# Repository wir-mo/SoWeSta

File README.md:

# SoWeSta
**So**lar powered **We**ather **Sta**tion

## PCB
You can view the pcb in your browser using [this link](https://kicanvas.org/?github=https%3A%2F%2Fgithub.com%2Fwir-mo%2FSoWeSta%2Ftree%2Fmain%2Fpcb)

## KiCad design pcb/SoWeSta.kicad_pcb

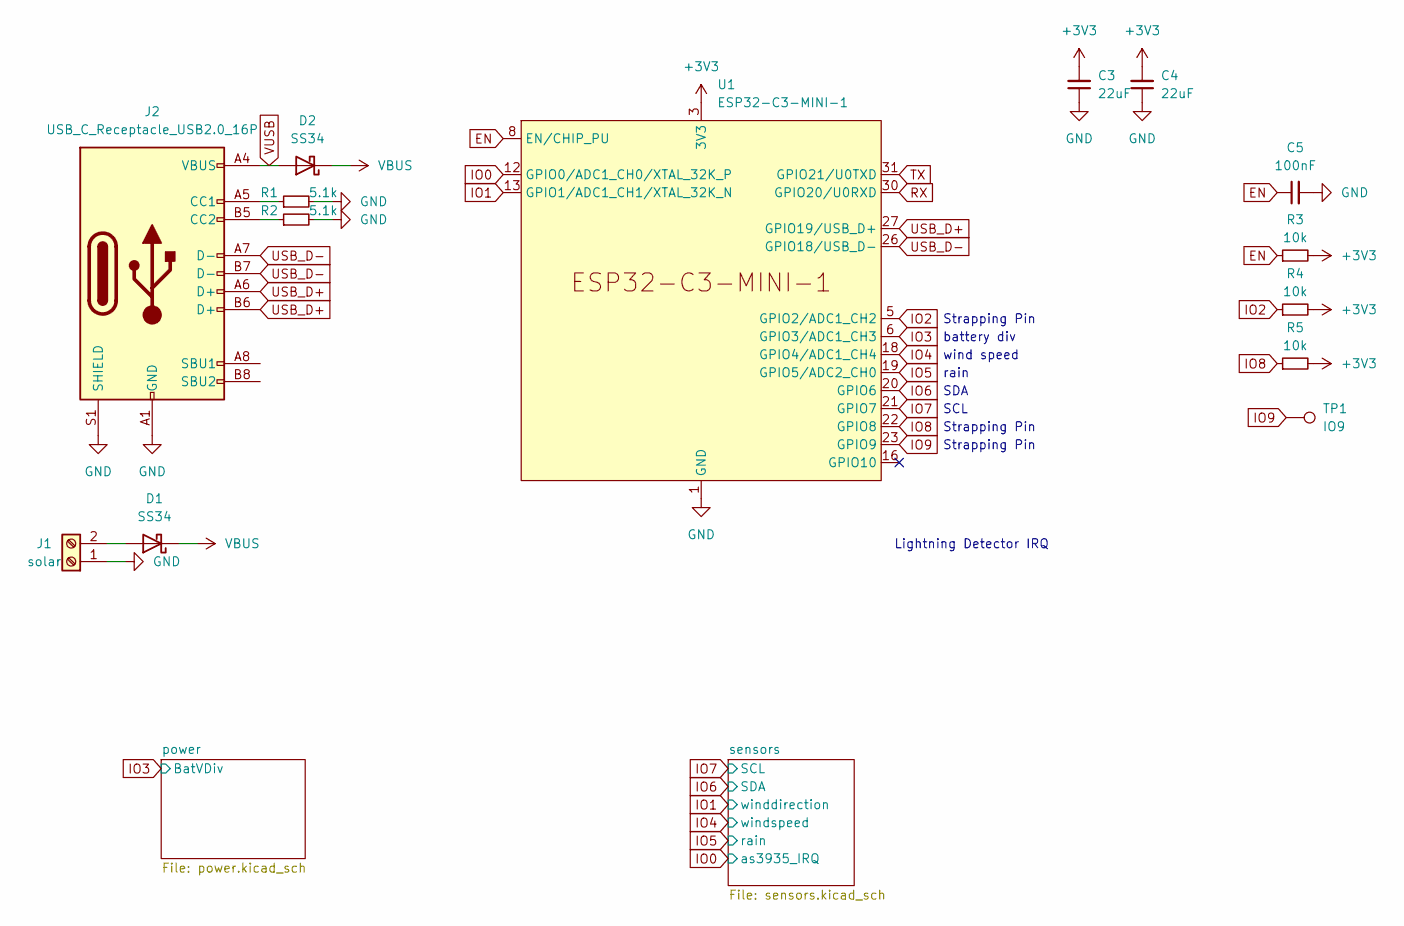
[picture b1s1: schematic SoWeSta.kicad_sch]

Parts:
C3, C4: 22uF; C_0603_1608Metric
C5: 100nF; C_0603_1608Metric
D1, D2: SS34; D_SMA
J1: solar; PhoenixContact_MC_1,5_2-G-3.5_1x02_P3.50mm_Horizontal
J2: USB_C_Receptacle_USB2.0_16P; USB_C_Receptacle_GCT_USB4105-xx-A_16P_TopMnt_Horizontal
R1, R2: 5.1k; R_0603_1608Metric
R3, R4, R5: 10k; R_0603_1608Metric
TP1: IO9; TestPoint_Pad_D1.0mm
U1: ESP32-C3-MINI-1

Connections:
+3V3: C3.2, C4.2, R3.2, R4.2, R5.2, U1.3 (3V3); also elsewhere on the board
EN: C5.1, R3.1, U1.8 (EN/CHIP_PU)
GND: C3.1, C4.1, C5.2, J1.1, J2.A1 (GND), J2.A12 (GND), J2.B1 (GND), J2.B12 (GND), J2.S1 (SHIELD), R1.2, R2.2, U1.1 (GND), U1.2 (GND), U1.11 (GND), U1.14 (GND), U1.36 (GND), U1.37 (GND), U1.38 (GND), U1.39 (GND), U1.40 (GND), U1.41 (GND), U1.42 (GND), U1.43 (GND), U1.44 (GND), U1.45 (GND), U1.46 (GND), U1.47 (GND), U1.48 (GND), U1.49 (GND), U1.50 (GND), U1.51 (GND), U1.52 (GND), U1.53 (GND); also elsewhere on the board
IO0: U1.12 (GPIO0/ADC1_CH0/XTAL_32K_P); also elsewhere on the board
IO1: U1.13 (GPIO1/ADC1_CH1/XTAL_32K_N); also elsewhere on the board
IO2: R4.1, U1.5 (GPIO2/ADC1_CH2)
IO3: U1.6 (GPIO3/ADC1_CH3); also elsewhere on the board
IO4: U1.18 (GPIO4/ADC1_CH4); also elsewhere on the board
IO5: U1.19 (GPIO5/ADC2_CH0); also elsewhere on the board
IO6: U1.20 (GPIO6); also elsewhere on the board
IO7: U1.21 (GPIO7); also elsewhere on the board
IO8: R5.1, U1.22 (GPIO8)
IO9: TP1.1, U1.23 (GPIO9)
unnamed: D1.2 (A), J1.2
unnamed: J2.A5 (CC1), R1.1
unnamed: J2.B5 (CC2), R2.1
RX: U1.30 (GPIO20/U0RXD); also elsewhere on the board
TX: U1.31 (GPIO21/U0TXD); also elsewhere on the board
USB_D+: J2.A6 (D+), J2.B6 (D+), U1.27 (GPIO19/USB_D+)
USB_D-: J2.A7 (D-), J2.B7 (D-), U1.26 (GPIO18/USB_D-)
VBUS: D1.1 (K), D2.1 (K); also elsewhere on the board
VUSB: D2.2 (A), J2.A4 (VBUS), J2.A9 (VBUS), J2.B4 (VBUS), J2.B9 (VBUS); also elsewhere on the board

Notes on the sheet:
SCL
battery div
wind speed
Lightning Detector IRQ
Strapping Pin
rain
SDA

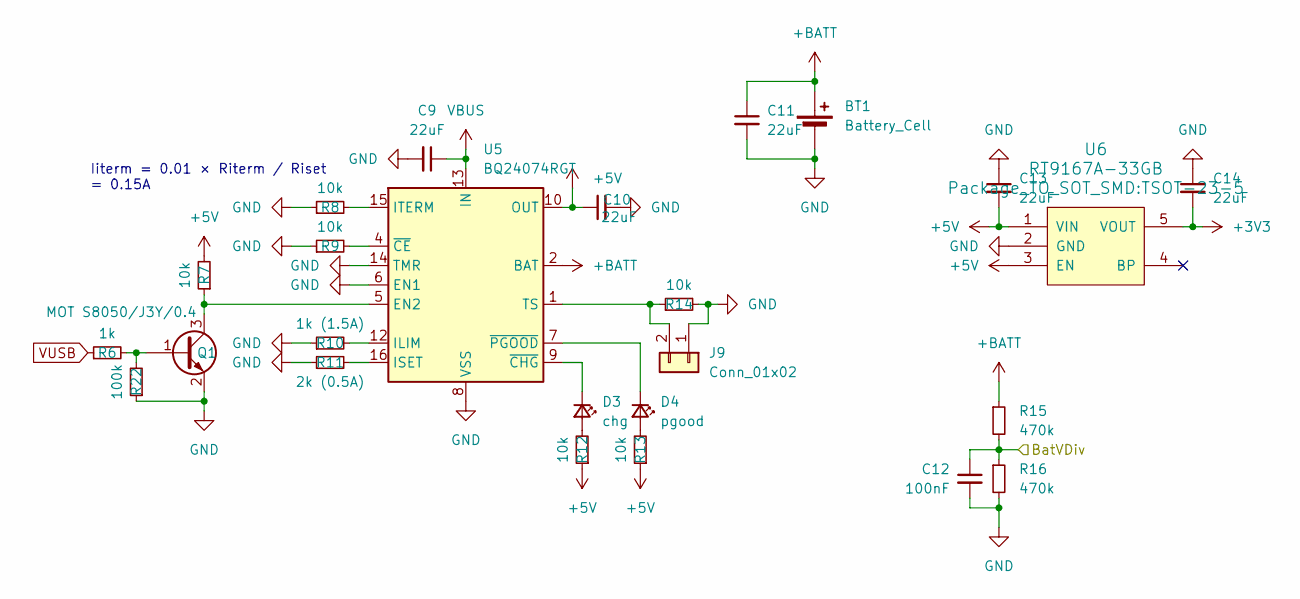
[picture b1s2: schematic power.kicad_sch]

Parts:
BT1: Battery_Cell; BH-18650-B1BA002
C9, C10, C11, C13, C14: 22uF; C_0603_1608Metric
C12: 100nF; C_0603_1608Metric
D3: chg; LED_0603_1608Metric
D4: pgood; LED_0603_1608Metric
J9: Conn_01x02; PinHeader_1x02_P2.54mm_Vertical
Q1: MOT S8050/J3Y/0.4; SOT-23
R6: 1k; R_0603_1608Metric
R7, R8, R9, R12, R13, R14: 10k; R_0603_1608Metric
R10: 1k (1.5A); R_0603_1608Metric
R11: 2k (0.5A); R_0603_1608Metric
R15, R16: 470k; R_0603_1608Metric
R22: 100k; R_0603_1608Metric
U5: BQ24074RGT; VQFN-16-1EP_3x3mm_P0.5mm_EP1.6x1.6mm
U6: RT9167A-33GB; TSOT-23-5

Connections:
+3V3: C14.2, U6.5 (VOUT); also elsewhere on the board
+5V: C10.1, C13.2, R7.2, R12.1, R13.1, U5.10 (OUT), U5.11 (OUT), U6.1 (VIN), U6.3 (EN); also elsewhere on the board
+BATT: BT1.1 (+), C11.1, R15.1, U5.2 (BAT), U5.3 (BAT)
GND: BT1.2 (-), C9.2, C10.2, C11.2, C12.2, C13.1, C14.1, J9.1, Q1.2 (E), R8.1, R9.1, R10.1, R11.1, R14.2, R16.2, R22.1, U5.6 (EN1), U5.8 (VSS), U5.14 (TMR), U5.17 (VSS), U6.2 (GND); also elsewhere on the board
IO3: C12.1, R15.2, R16.1; also elsewhere on the board
unnamed: D3.2 (A), R12.2
unnamed: D3.1 (K), U5.9 (~CHG)
unnamed: D4.2 (A), R13.2
unnamed: D4.1 (K), U5.7 (~PGOOD)
unnamed: J9.2, R14.1, U5.1 (TS)
unnamed: Q1.1 (B), R6.2, R22.2
unnamed: Q1.3 (C), R7.1, U5.5 (EN2)
unnamed: R10.2, U5.12 (ILIM)
unnamed: R11.2, U5.16 (ISET)
unnamed: R8.2, U5.15 (ITERM)
unnamed: R9.2, U5.4 (~CE)
VBUS: C9.1, U5.13 (IN); also elsewhere on the board
VUSB: R6.1; also elsewhere on the board

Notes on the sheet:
Iiterm = 0.01 × Riterm / Riset = 0.15A

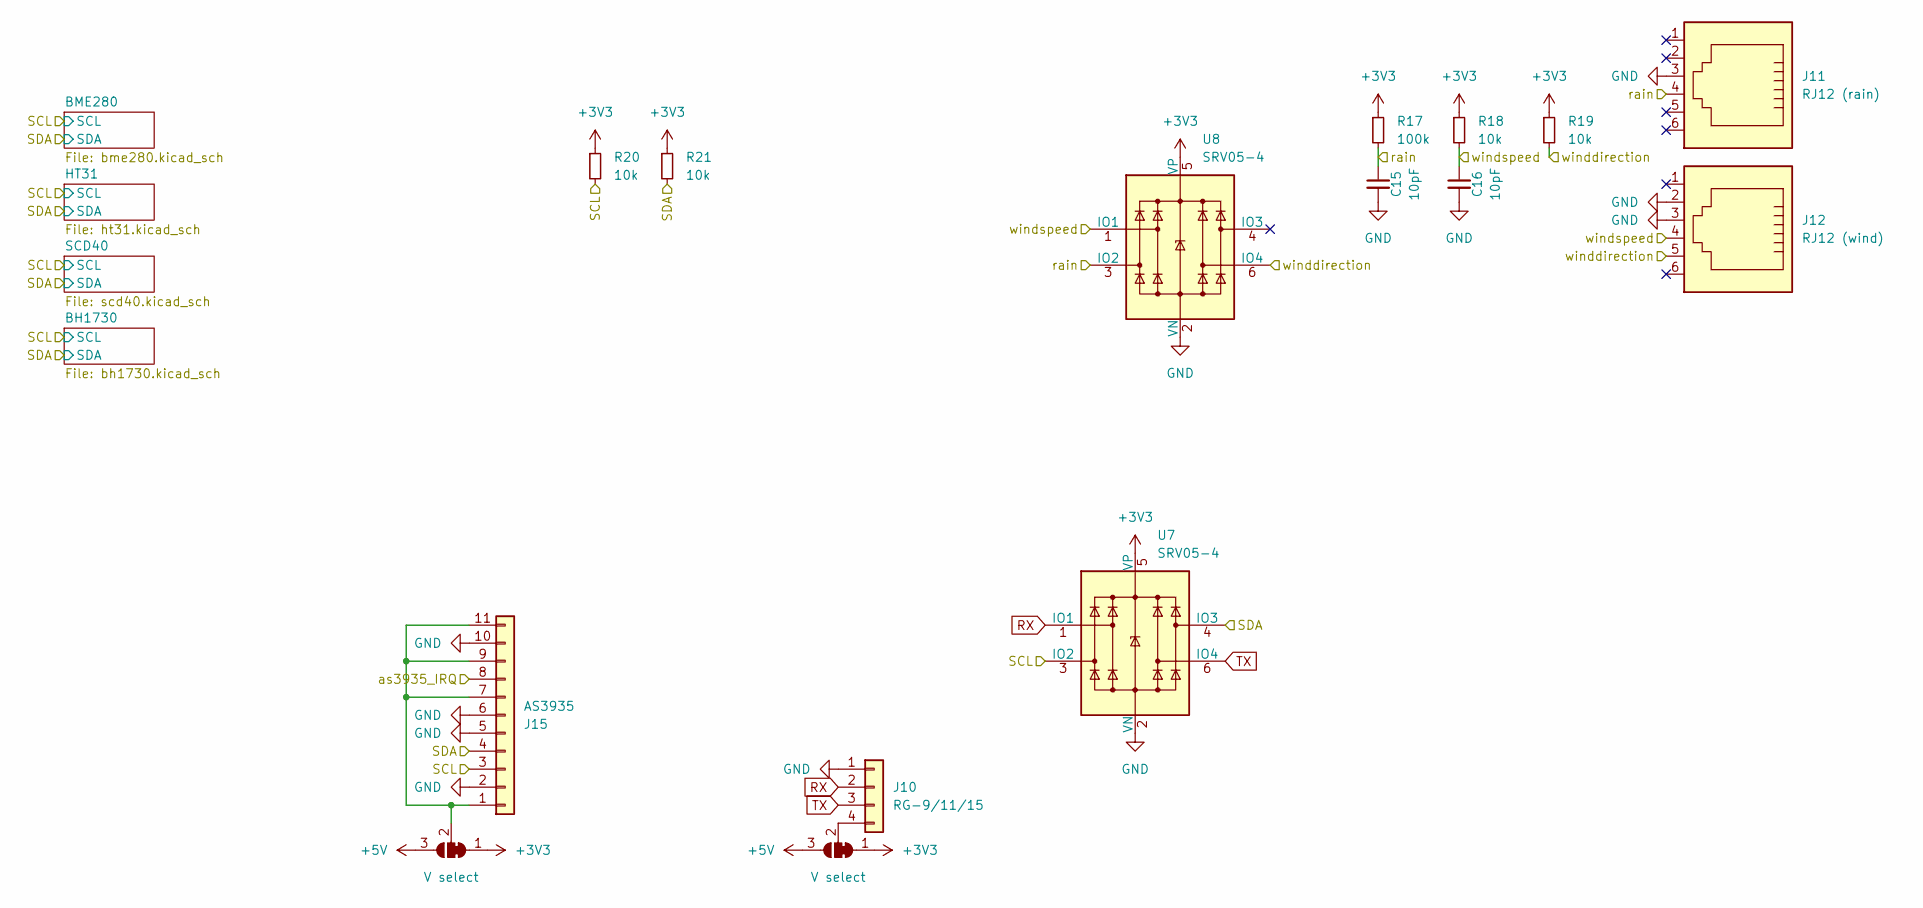
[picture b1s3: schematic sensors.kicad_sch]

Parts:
C15, C16: 10pF; C_0603_1608Metric
J10: RG-9/11/15; PinSocket_1x04_P2.54mm_Vertical
J11: RJ12 (rain); RJ25_Wayconn_MJEA-660X1_Horizontal
J12: RJ12 (wind); RJ25_Wayconn_MJEA-660X1_Horizontal
J15: AS3935; PinSocket_1x11_P2.54mm_Vertical
JP4, JP6: V select; SolderJumper-3_P1.3mm_Bridged12_RoundedPad1.0x1.5mm
R17: 100k; R_0603_1608Metric
R18, R19, R20, R21: 10k; R_0603_1608Metric
U7, U8: SRV05-4; SOT-23-6

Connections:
+3V3: JP4.1 (A), JP6.1 (A), R17.1, R18.1, R19.1, R20.1, R21.1, U7.5 (VP), U8.5 (VP); also elsewhere on the board
+5V: JP4.3 (B), JP6.3 (B); also elsewhere on the board
GND: C15.2, C16.2, J10.1, J11.3, J12.2, J12.3, J15.2, J15.5, J15.6, J15.10, U7.2 (VN), U8.2 (VN); also elsewhere on the board
IO0: J15.8; also elsewhere on the board
IO1: J12.5, R19.2, U8.6 (IO4); also elsewhere on the board
IO4: C16.1, J12.4, R18.2, U8.1 (IO1); also elsewhere on the board
IO5: C15.1, J11.4, R17.2, U8.3 (IO2); also elsewhere on the board
IO6: J15.4, R21.2, U7.4 (IO3); also elsewhere on the board
IO7: J15.3, R20.2, U7.3 (IO2); also elsewhere on the board
unnamed: J10.4, JP4.2 (C)
unnamed: J15.1, J15.7, J15.9, J15.11, JP6.2 (C)
RX: J10.2, U7.1 (IO1); also elsewhere on the board
TX: J10.3, U7.6 (IO4); also elsewhere on the board

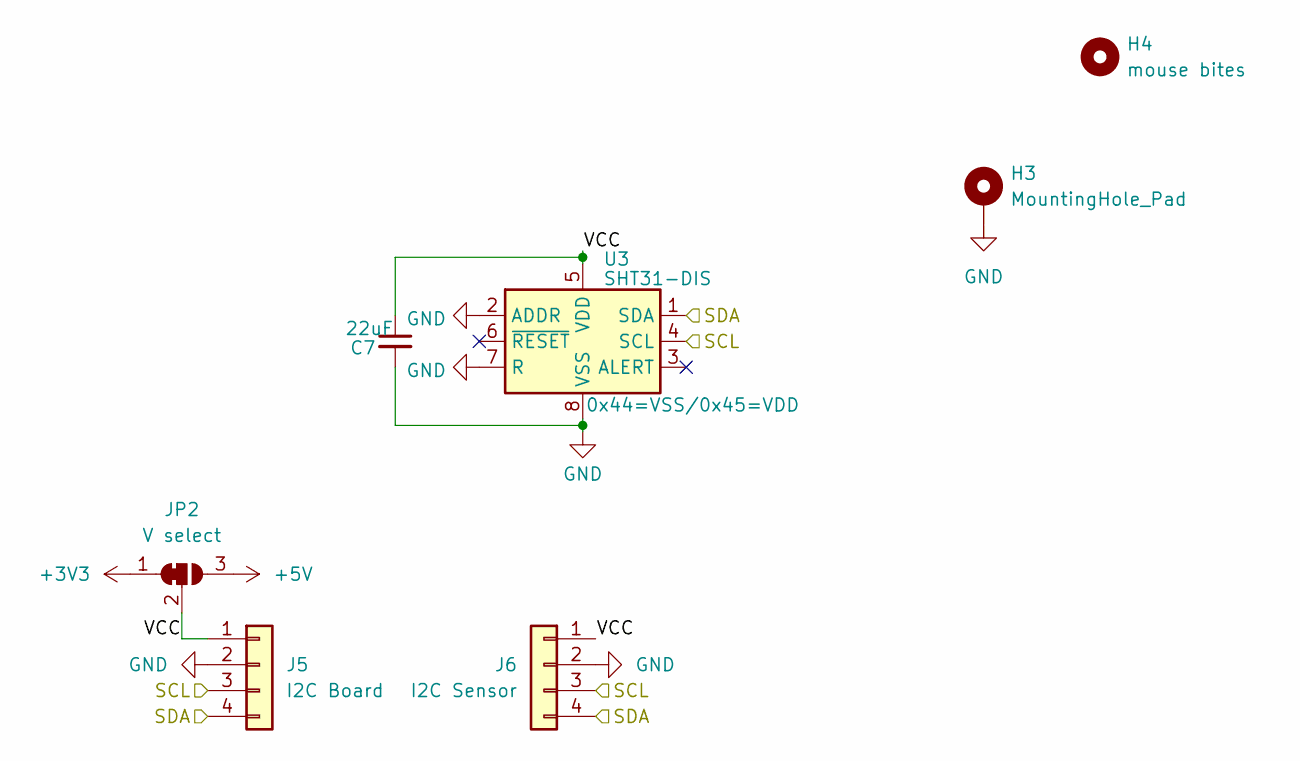
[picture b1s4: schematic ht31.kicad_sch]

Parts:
C7: 22uF; C_0603_1608Metric
H3: MountingHole_Pad; MountingHole_3.2mm_M3_Pad
H4: mouse bites; mouse-bite-3mm-slot
J5: I2C Board; PinSocket_1x04_P2.54mm_Vertical
J6: I2C Sensor; PinHeader_1x04_P2.54mm_Vertical
JP2: V select; SolderJumper-3_P1.3mm_Bridged12_RoundedPad1.0x1.5mm
U3: SHT31-DIS; Sensirion_DFN-8-1EP_2.5x2.5mm_P0.5mm_EP1.1x1.7mm

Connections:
+3V3: JP2.1 (A); also elsewhere on the board
+5V: JP2.3 (B); also elsewhere on the board
/sensors/HT31/VCC: C7.1, J5.1, J6.1, JP2.2 (C), U3.5 (VDD)
GND: C7.2, H3.1, J5.2, J6.2, U3.2 (ADDR), U3.7 (R), U3.8 (VSS), U3.9 (VSS); also elsewhere on the board
IO6: J5.4, J6.4, U3.1 (SDA); also elsewhere on the board
IO7: J5.3, J6.3, U3.4 (SCL); also elsewhere on the board

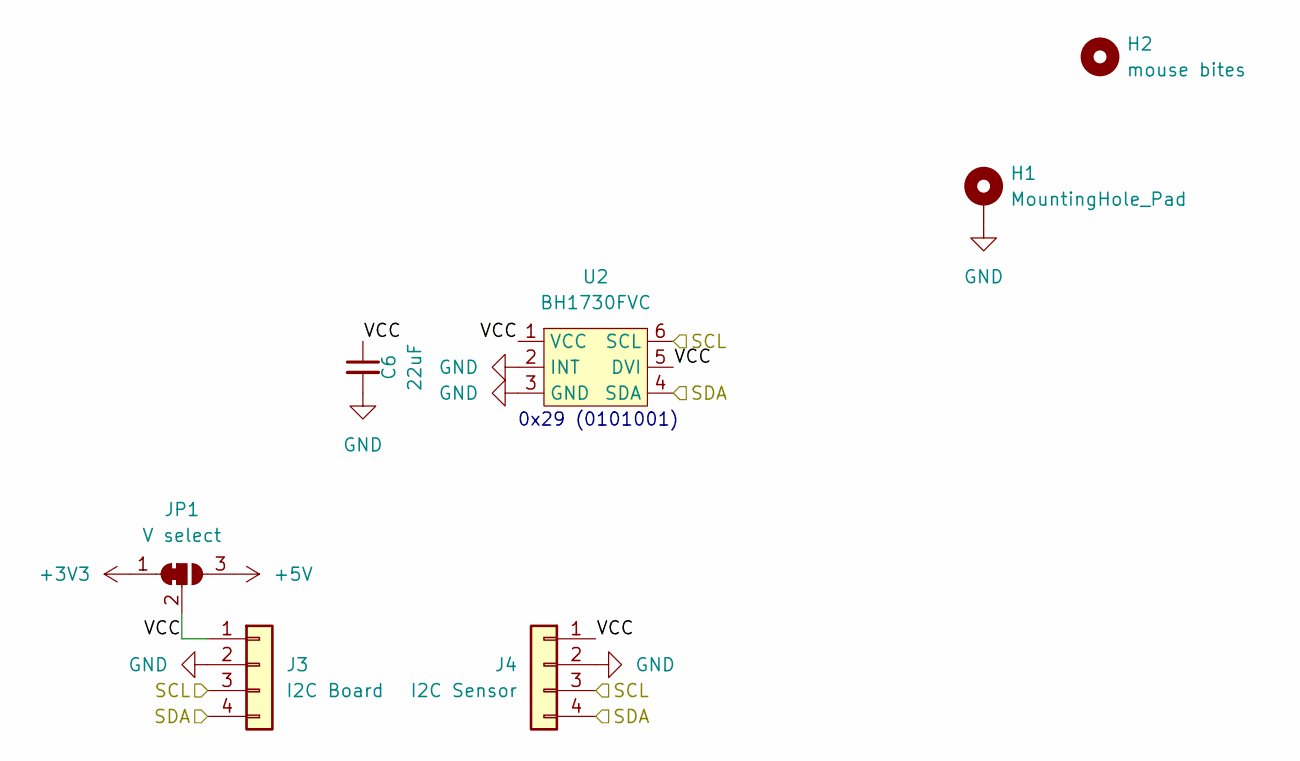
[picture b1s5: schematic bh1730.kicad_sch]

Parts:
C6: 22uF; C_0603_1608Metric
H1: MountingHole_Pad; MountingHole_3.2mm_M3_Pad
H2: mouse bites; mouse-bite-3mm-slot
J3: I2C Board; PinSocket_1x04_P2.54mm_Vertical
J4: I2C Sensor; PinHeader_1x04_P2.54mm_Vertical
JP1: V select; SolderJumper-3_P1.3mm_Bridged12_RoundedPad1.0x1.5mm
U2: BH1730FVC; WSOF6

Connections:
+3V3: JP1.1 (A); also elsewhere on the board
+5V: JP1.3 (B); also elsewhere on the board
/sensors/BH1730/VCC: C6.1, J3.1, J4.1, JP1.2 (C), U2.1 (VCC), U2.5 (DVI)
GND: C6.2, H1.1, J3.2, J4.2, U2.2 (INT), U2.3 (GND); also elsewhere on the board
IO6: J3.4, J4.4, U2.4 (SDA); also elsewhere on the board
IO7: J3.3, J4.3, U2.6 (SCL); also elsewhere on the board

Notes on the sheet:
0x29 (0101001)

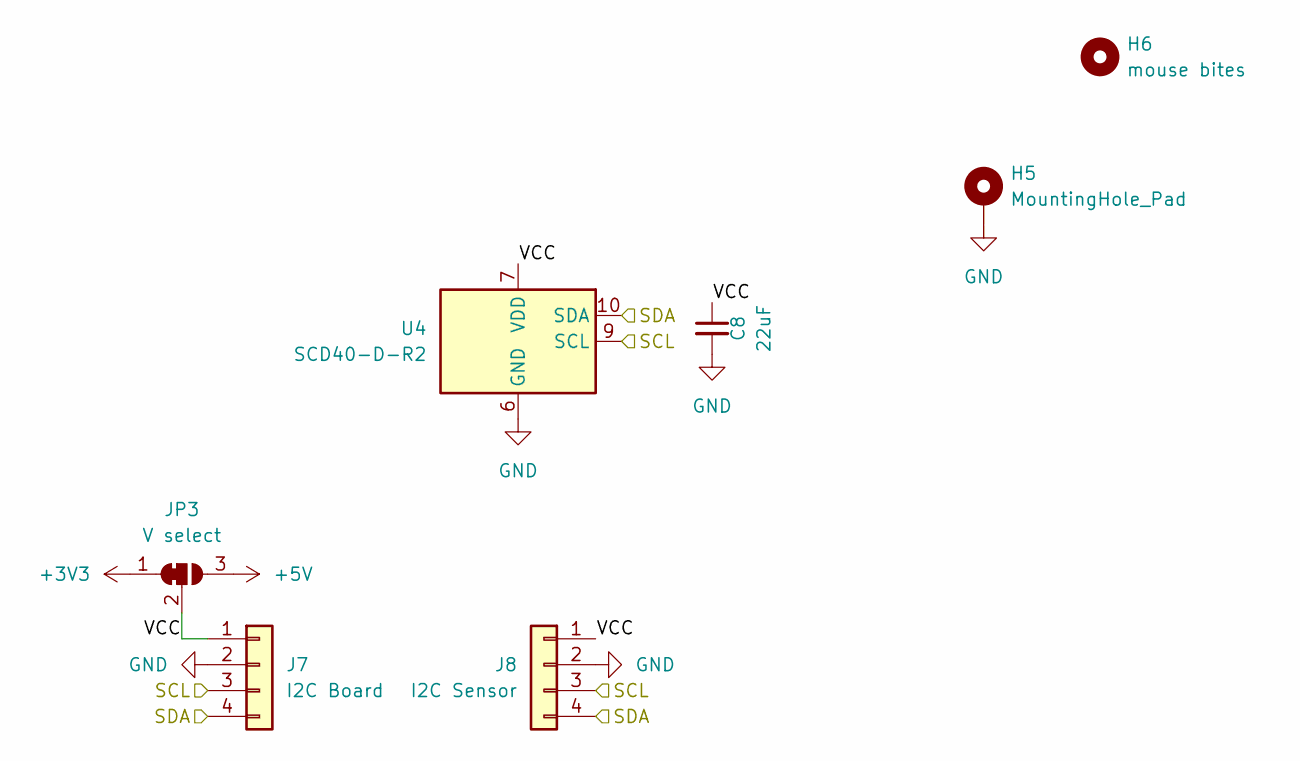
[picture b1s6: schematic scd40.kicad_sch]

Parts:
C8: 22uF; C_0603_1608Metric
H5: MountingHole_Pad; MountingHole_3.2mm_M3_Pad
H6: mouse bites; mouse-bite-3mm-slot
J7: I2C Board; PinSocket_1x04_P2.54mm_Vertical
J8: I2C Sensor; PinHeader_1x04_P2.54mm_Vertical
JP3: V select; SolderJumper-3_P1.3mm_Bridged12_RoundedPad1.0x1.5mm
U4: SCD40-D-R2; Sensirion_SCD4x-1EP_10.1x10.1mm_P1.25mm_EP4.8x4.8mm

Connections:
+3V3: JP3.1 (A); also elsewhere on the board
+5V: JP3.3 (B); also elsewhere on the board
/sensors/SCD40/VCC: C8.1, J7.1, J8.1, JP3.2 (C), U4.7 (VDD), U4.19 (VDD)
GND: C8.2, H5.1, J7.2, J8.2, U4.6 (GND), U4.20 (GND), U4.21 (GND); also elsewhere on the board
IO6: J7.4, J8.4, U4.10 (SDA); also elsewhere on the board
IO7: J7.3, J8.3, U4.9 (SCL); also elsewhere on the board

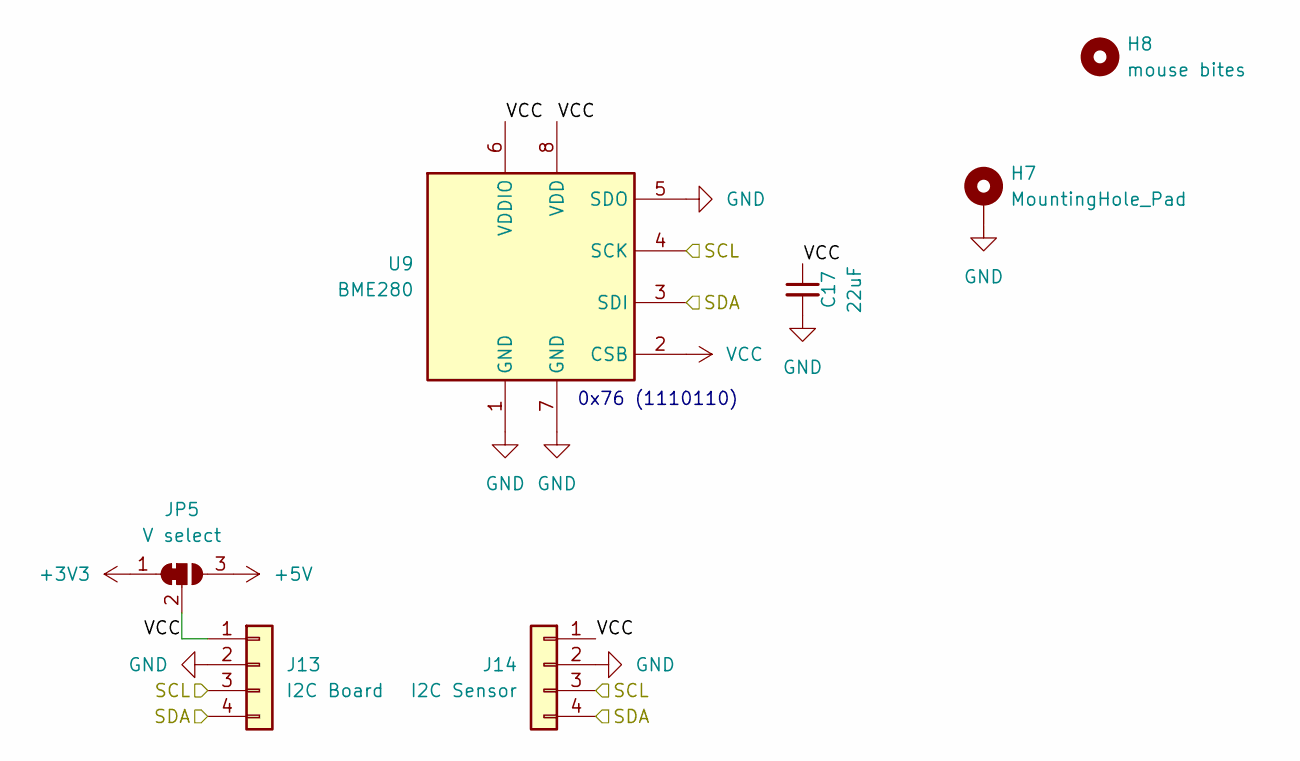
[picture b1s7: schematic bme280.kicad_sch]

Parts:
C17: 22uF; C_0603_1608Metric
H7: MountingHole_Pad; MountingHole_3.2mm_M3_Pad
H8: mouse bites; mouse-bite-3mm-slot
J13: I2C Board; PinSocket_1x04_P2.54mm_Vertical
J14: I2C Sensor; PinHeader_1x04_P2.54mm_Vertical
JP5: V select; SolderJumper-3_P1.3mm_Bridged12_RoundedPad1.0x1.5mm
U9: BME280; Bosch_LGA-8_2.5x2.5mm_P0.65mm_ClockwisePinNumbering

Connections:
+3V3: JP5.1 (A); also elsewhere on the board
+5V: JP5.3 (B); also elsewhere on the board
GND: C17.2, H7.1, J13.2, J14.2, U9.1 (GND), U9.5 (SDO), U9.7 (GND); also elsewhere on the board
IO6: J13.4, J14.4, U9.3 (SDI); also elsewhere on the board
IO7: J13.3, J14.3, U9.4 (SCK); also elsewhere on the board
VCC: C17.1, J13.1, J14.1, JP5.2 (C), U9.2 (CSB), U9.6 (VDDIO), U9.8 (VDD)

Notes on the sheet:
0x76 (1110110)

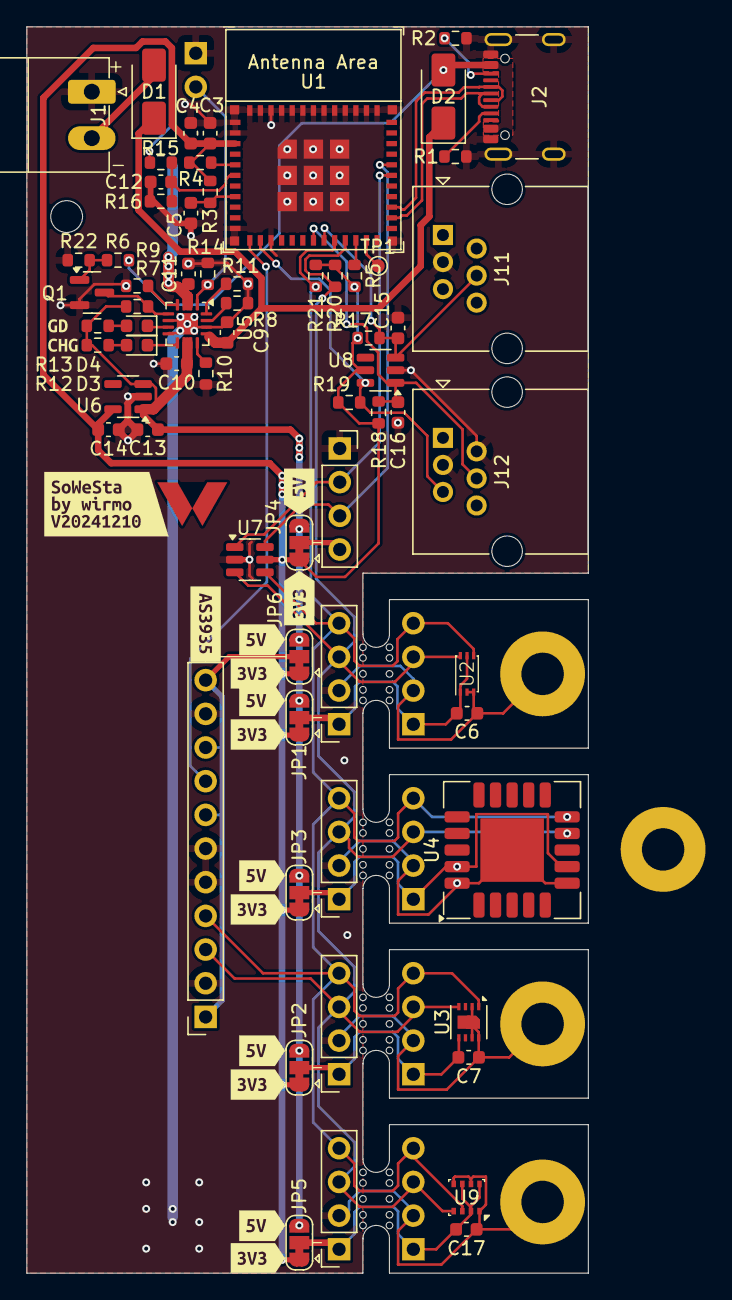
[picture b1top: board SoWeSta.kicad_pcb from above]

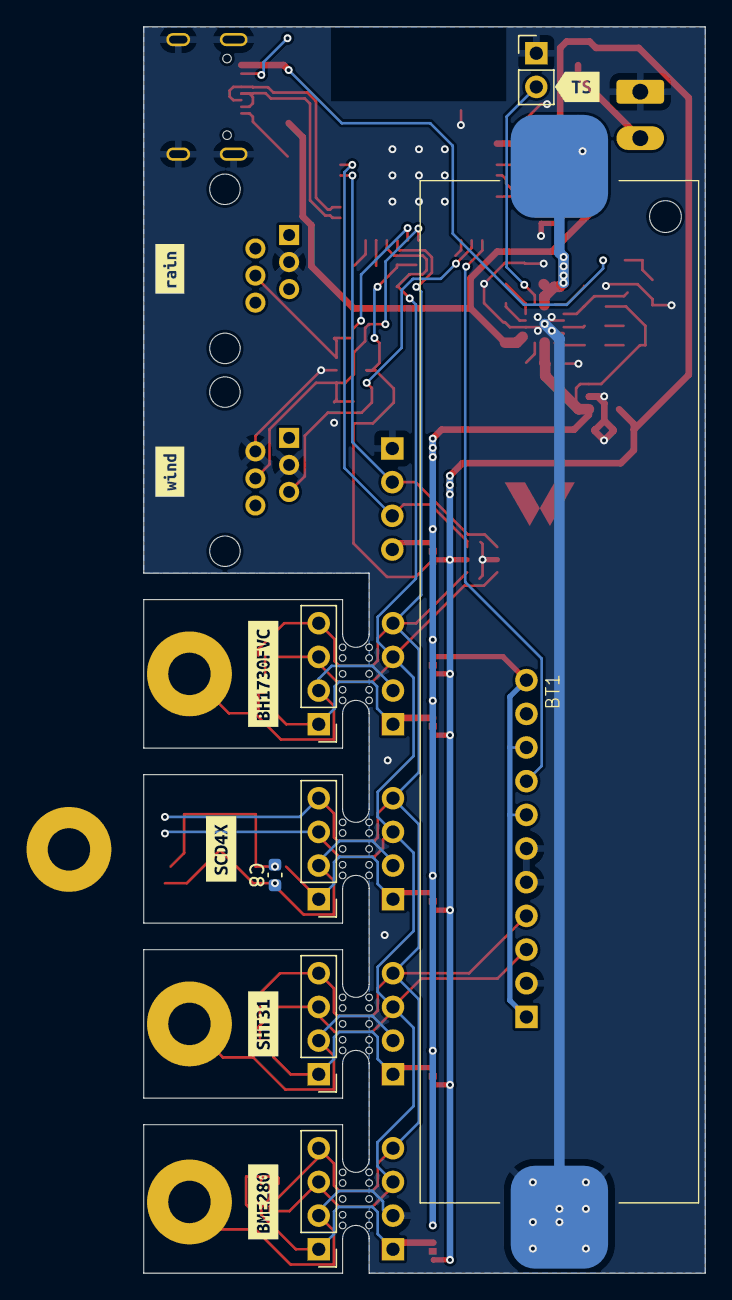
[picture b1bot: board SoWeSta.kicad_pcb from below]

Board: 2 copper layers, 42.4 x 94.0 mm, 105 parts (14 on the bottom side), 41 nets.

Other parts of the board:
kibuzzard-66DB4B6F, kibuzzard-66DB4B6F#2, kibuzzard-66DB4B6F#3, kibuzzard-66DB4B6F#4, kibuzzard-66DB4B6F#5, kibuzzard-66DB4B6F#6: G***; kibuzzard-66DB4B6F
kibuzzard-66DB4BF3: G***; kibuzzard-66DB4BF3
kibuzzard-66DB4CC2, kibuzzard-66DB4CC2#2, kibuzzard-66DB4CC2#3, kibuzzard-66DB4CC2#4, kibuzzard-66DB4CC2#5: G***; kibuzzard-66DB4CC2
kibuzzard-66DB4ECF: G***; kibuzzard-66DB4ECF
kibuzzard-66DB4EDB: G***; kibuzzard-66DB4EDB
kibuzzard-6758A59F: G***; kibuzzard-6758A59F
kibuzzard-67419C7E: G***; kibuzzard-67419C7E
kibuzzard-67419CC9: G***; kibuzzard-67419CC9
kibuzzard-67419D00: G***; kibuzzard-67419D00
kibuzzard-67419D7C: G***; kibuzzard-67419D7C
kibuzzard-67419D22: G***; kibuzzard-67419D22
kibuzzard-67419EEB: G***; kibuzzard-67419EEB
kibuzzard-67291623: G***; kibuzzard-67291623
kibuzzard-67291638: G***; kibuzzard-67291638

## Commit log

2024-08-14 Initial PCB commit
2024-08-14 Add more sensors and start layout
    - BH1730FVC
    - BME280
    - RG-9/11/15
2024-09-05 Finalize rough PCB version
    - Split sensors into own sub schematic as well as sub-sub sensor schematics
    - Split piwer into own sub schematic
2025-02-14 Ignore kicad production and macos files
2025-02-14 Rename pcb, add sensors and fix some issues
2025-02-14 Initial housing commit
2025-02-14 Add link to view pcb
